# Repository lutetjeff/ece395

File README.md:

Repository for UIUC ECE395 project known as RHipoff. A mixture of the Rhythm Horizon and RE:Flex Dance platforms built from the ground up.
Current configuration is for four load cells only, but firmware supports up to 16 different panels with four load cells each.

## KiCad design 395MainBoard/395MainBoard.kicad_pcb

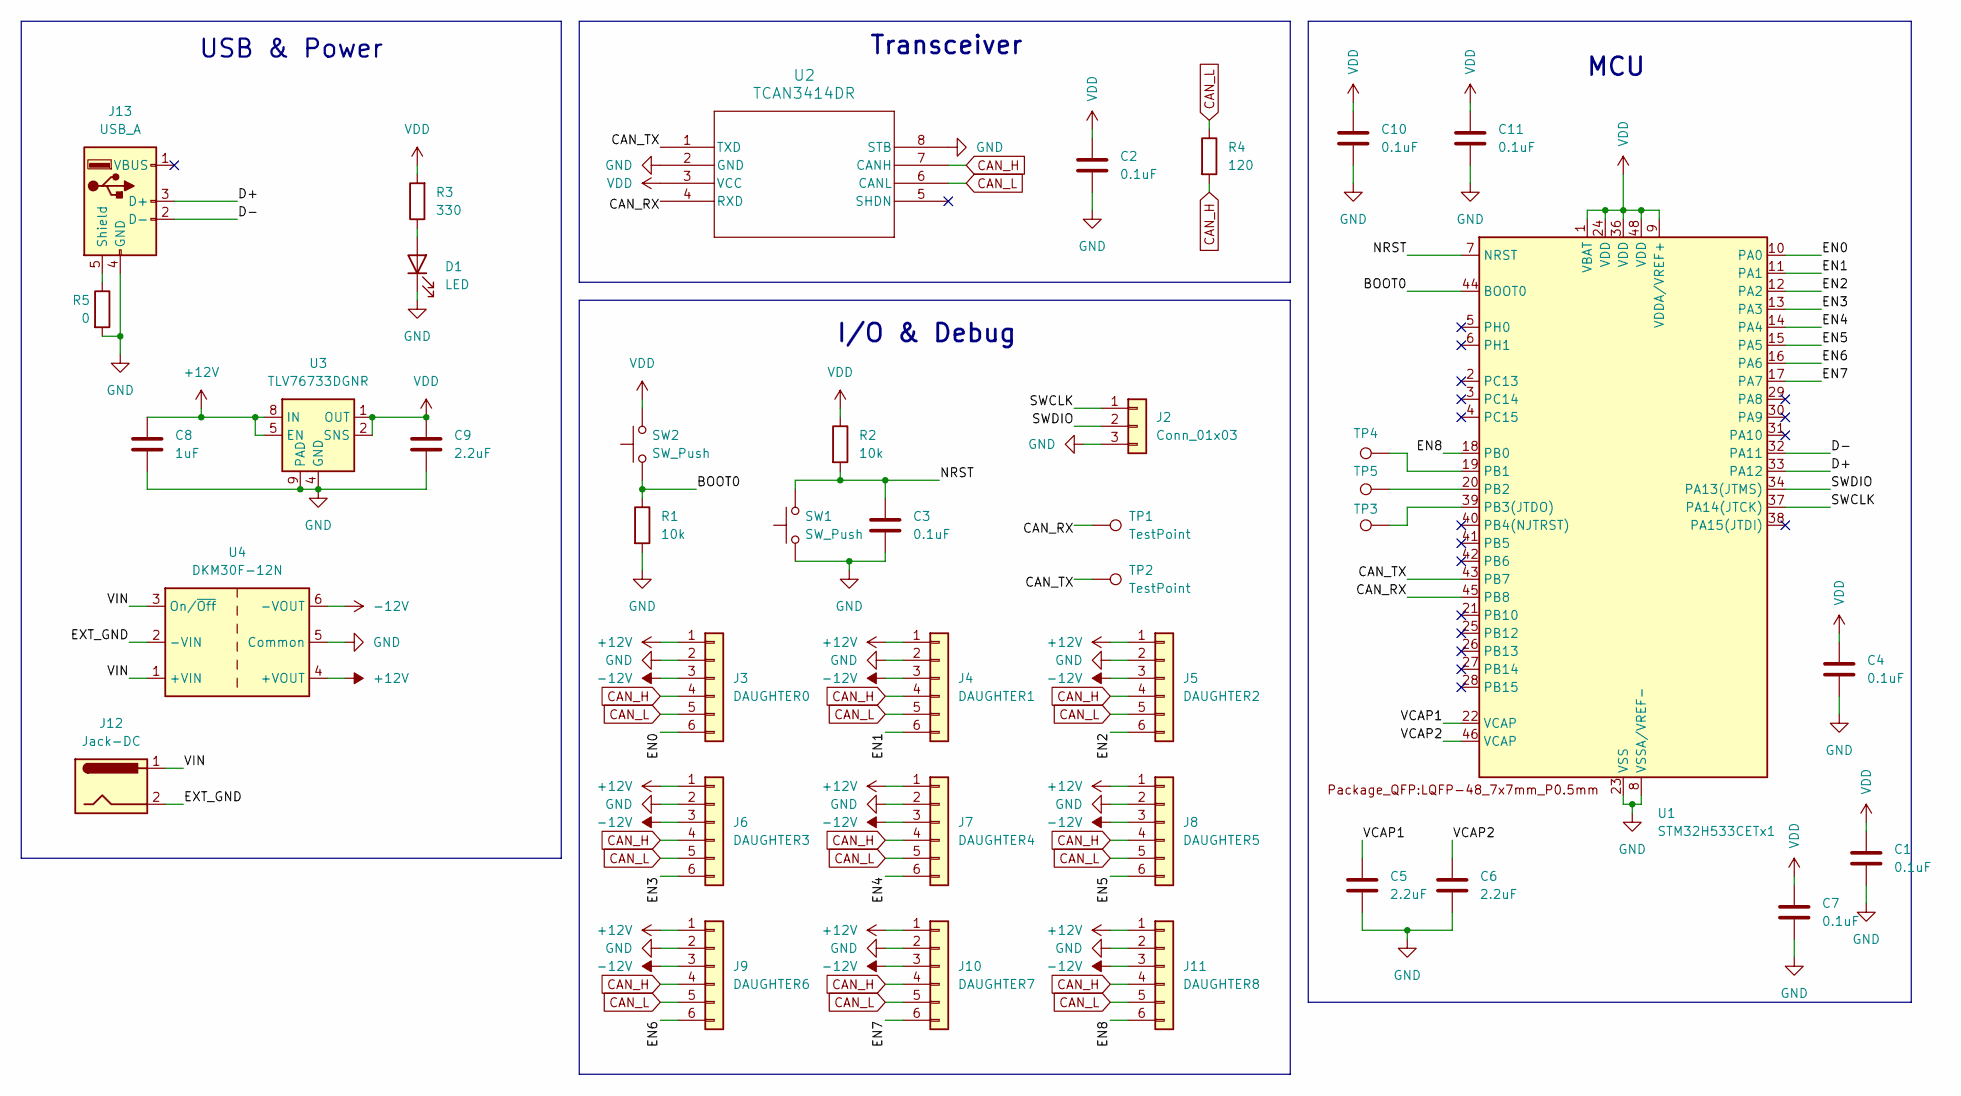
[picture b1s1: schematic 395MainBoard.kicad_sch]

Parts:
C1, C2, C3, C4, C7, C10, C11: 0.1uF; C_0805_2012Metric_Pad1.18x1.45mm_HandSolder
C5, C6, C9: 2.2uF; C_0805_2012Metric_Pad1.18x1.45mm_HandSolder
C8: 1uF; C_0805_2012Metric_Pad1.18x1.45mm_HandSolder
D1: LED; LED_0805_2012Metric_Pad1.15x1.40mm_HandSolder
J2: Conn_01x03; JST_XH_B3B-XH-A_1x03_P2.50mm_Vertical
J3: DAUGHTER0; JST_XH_B6B-XH-A_1x06_P2.50mm_Vertical
J4: DAUGHTER1; JST_XH_B6B-XH-A_1x06_P2.50mm_Vertical
J5: DAUGHTER2; JST_XH_B6B-XH-A_1x06_P2.50mm_Vertical
J6: DAUGHTER3; JST_XH_B6B-XH-A_1x06_P2.50mm_Vertical
J7: DAUGHTER4; JST_XH_B6B-XH-A_1x06_P2.50mm_Vertical
J8: DAUGHTER5; JST_XH_B6B-XH-A_1x06_P2.50mm_Vertical
J9: DAUGHTER6; JST_XH_B6B-XH-A_1x06_P2.50mm_Vertical
J10: DAUGHTER7; JST_XH_B6B-XH-A_1x06_P2.50mm_Vertical
J11: DAUGHTER8; JST_XH_B6B-XH-A_1x06_P2.50mm_Vertical
J12: Jack-DC; BarrelJack_Horizontal
J13: USB_A; USB_A_Molex_67643_Horizontal
R1, R2: 10k; R_0805_2012Metric_Pad1.20x1.40mm_HandSolder
R3: 330; R_0805_2012Metric_Pad1.20x1.40mm_HandSolder
R4: 120; R_0805_2012Metric_Pad1.20x1.40mm_HandSolder
R5: 0; R_0805_2012Metric_Pad1.20x1.40mm_HandSolder
SW1, SW2: SW_Push; SW_PUSH_6mm
TP1, TP2, TP3, TP4, TP5: TestPoint; TestPoint_Pad_D2.0mm
U1: STM32H533CETx1; LQFP-48_7x7mm_P0.5mm
U2: TCAN3414DR; SOIC-8_3.9x4.9mm_P1.27mm
U3: TLV76733DGNR; VSSOP-8_3x3mm_P0.65mm
U4: DKM30F-12N

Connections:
+12V: C8.1, J3.1, J4.1, J5.1, J6.1, J7.1, J8.1, J9.1, J10.1, J11.1, U3.5 (EN), U3.8 (IN), U4.4 (+VOUT)
-12V: J3.3, J4.3, J5.3, J6.3, J7.3, J8.3, J9.3, J10.3, J11.3, U4.6 (-VOUT)
/BOOT0: R1.1, SW2.1, U1.44 (BOOT0)
/CAN_RX: TP1.1, U1.45 (PB8), U2.4 (RXD)
/CAN_TX: TP2.1, U1.43 (PB7), U2.1 (TXD)
/D+: J13.3 (D+), U1.33 (PA12)
/D-: J13.2 (D-), U1.32 (PA11)
/EN0: J3.6, U1.10 (PA0)
/EN1: J4.6, U1.11 (PA1)
/EN2: J5.6, U1.12 (PA2)
/EN3: J6.6, U1.13 (PA3)
/EN4: J7.6, U1.14 (PA4)
/EN5: J8.6, U1.15 (PA5)
/EN6: J9.6, U1.16 (PA6)
/EN7: J10.6, U1.17 (PA7)
/EN8: J11.6, U1.18 (PB0)
/EXT_GND: J12.2, U4.2 (-VIN)
/NRST: C3.1, R2.2, SW1.2, U1.7 (NRST)
/SWCLK: J2.1, U1.37 (PA14(JTCK))
/SWDIO: J2.2, U1.34 (PA13(JTMS))
/VCAP1: C5.1, U1.22 (VCAP)
/VCAP2: C6.1, U1.46 (VCAP)
/VIN: J12.1, U4.1 (+VIN), U4.3 (On/~Off)
CAN_H: J3.4, J4.4, J5.4, J6.4, J7.4, J8.4, J9.4, J10.4, J11.4, R4.2, U2.7 (CANH)
CAN_L: J3.5, J4.5, J5.5, J6.5, J7.5, J8.5, J9.5, J10.5, J11.5, R4.1, U2.6 (CANL)
GND: C1.2, C2.2, C3.2, C4.2, C5.2, C6.2, C7.2, C8.2, C9.2, C10.2, C11.2, D1.1 (K), J2.3, J3.2, J4.2, J5.2, J6.2, J7.2, J8.2, J9.2, J10.2, J11.2, J13.4 (GND), R1.2, R5.2, SW1.1, U1.8 (VSSA/VREF-), U1.23 (VSS), U1.35 (VSS), U1.47 (VSS), U2.2 (GND), U2.8 (STB), U3.4 (GND), U3.6 (GND), U3.9 (PAD), U4.5 (Common)
unnamed: D1.2 (A), R3.1
unnamed: J13.5 (Shield), R5.1
unnamed: TP4.1, U1.19 (PB1)
unnamed: TP5.1, U1.20 (PB2)
unnamed: TP3.1, U1.39 (PB3(JTDO))
VDD: C1.1, C2.1, C4.1, C7.1, C9.1, C10.1, C11.1, R2.1, R3.2, SW2.2, U1.1 (VBAT), U1.9 (VDDA/VREF+), U1.24 (VDD), U1.36 (VDD), U1.48 (VDD), U2.3 (VCC), U3.1 (OUT), U3.2 (SNS)

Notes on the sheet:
I/O & Debug
USB & Power
Transceiver
MCU

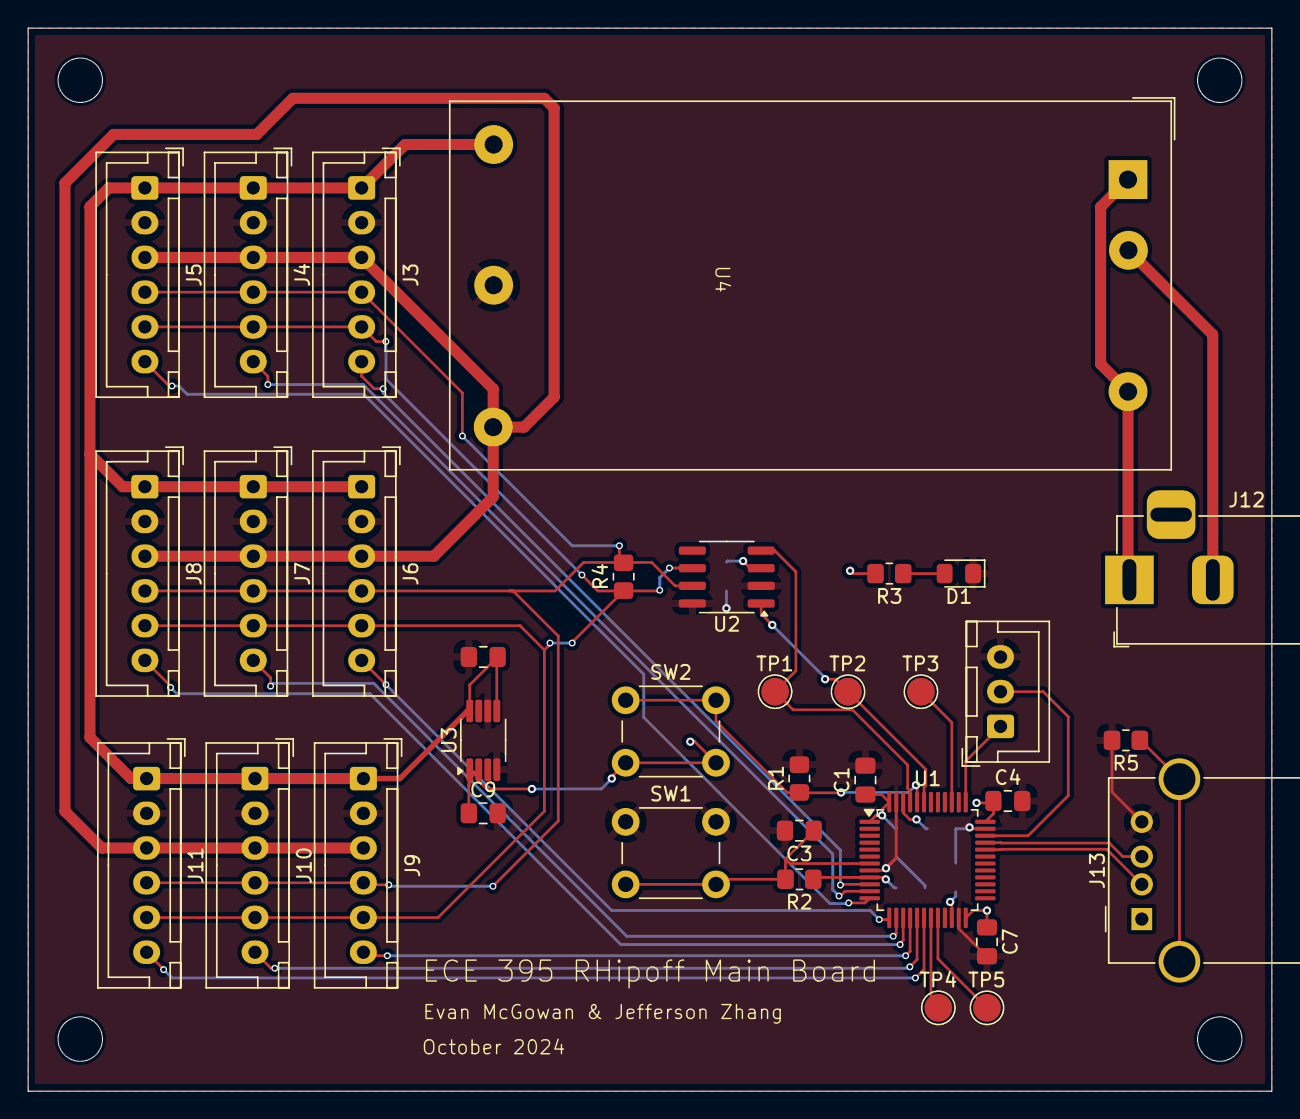
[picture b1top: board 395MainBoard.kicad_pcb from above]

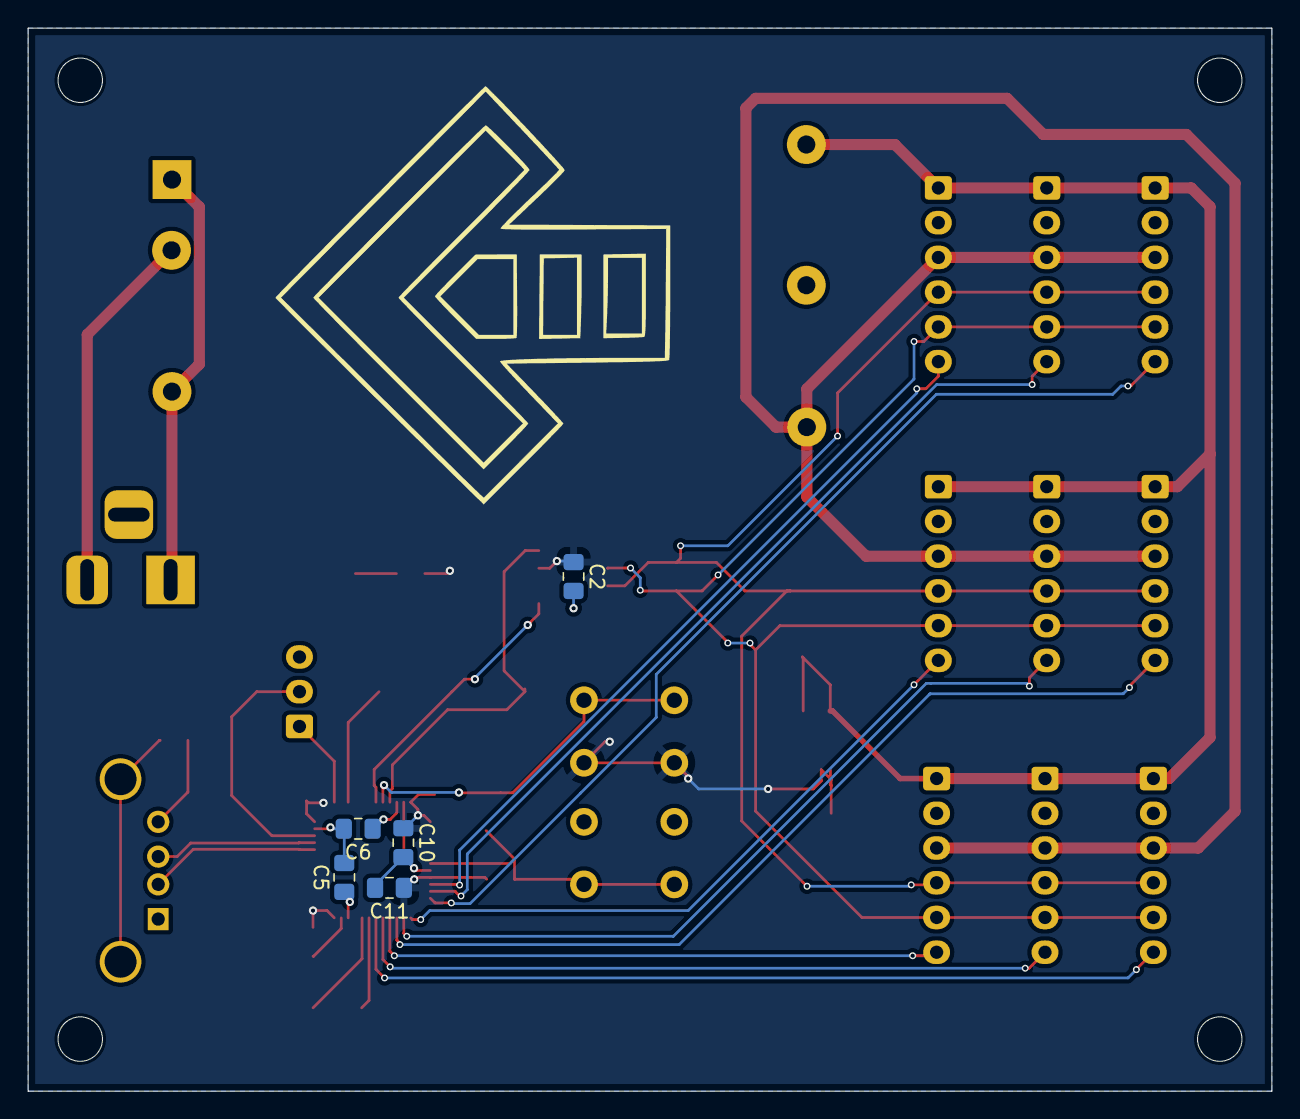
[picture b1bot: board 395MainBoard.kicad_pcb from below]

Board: 2 copper layers, 89.5 x 76.5 mm, 40 parts (5 on the bottom side), 32 nets.

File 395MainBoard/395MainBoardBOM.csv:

"Reference","Value","Datasheet","Footprint","Qty","DNP"
"C1,C2,C3,C4,C7,C10,C11","0.1uF","~","Capacitor_SMD:C_0805_2012Metric_Pad1.18x1.45mm_HandSolder","7",""
"C5,C6,C9","2.2uF","~","Capacitor_SMD:C_0805_2012Metric_Pad1.18x1.45mm_HandSolder","3",""
"C8","1uF","~","Capacitor_SMD:C_0805_2012Metric_Pad1.18x1.45mm_HandSolder","1",""
"D1","LED","~","LED_SMD:LED_0805_2012Metric_Pad1.15x1.40mm_HandSolder","1",""
"J2","Conn_01x03","~","Connector_JST:JST_XH_B3B-XH-A_1x03_P2.50mm_Vertical","1",""
"J3","DAUGHTER0","~","Connector_JST:JST_XH_B6B-XH-A_1x06_P2.50mm_Vertical","1",""
"J4","DAUGHTER1","~","Connector_JST:JST_XH_B6B-XH-A_1x06_P2.50mm_Vertical","1",""
"J5","DAUGHTER2","~","Connector_JST:JST_XH_B6B-XH-A_1x06_P2.50mm_Vertical","1",""
"J6","DAUGHTER3","~","Connector_JST:JST_XH_B6B-XH-A_1x06_P2.50mm_Vertical","1",""
"J7","DAUGHTER4","~","Connector_JST:JST_XH_B6B-XH-A_1x06_P2.50mm_Vertical","1",""
"J8","DAUGHTER5","~","Connector_JST:JST_XH_B6B-XH-A_1x06_P2.50mm_Vertical","1",""
"J9","DAUGHTER6","~","Connector_JST:JST_XH_B6B-XH-A_1x06_P2.50mm_Vertical","1",""
"J10","DAUGHTER7","~","Connector_JST:JST_XH_B6B-XH-A_1x06_P2.50mm_Vertical","1",""
"J11","DAUGHTER8","~","Connector_JST:JST_XH_B6B-XH-A_1x06_P2.50mm_Vertical","1",""
"J12","Jack-DC","~","Connector_BarrelJack:BarrelJack_Horizontal","1",""
"J13","USB_A","~","Connector_USB:USB_A_Molex_67643_Horizontal","1",""
"R1,R2","10k","~","Resistor_SMD:R_0805_2012Metric_Pad1.20x1.40mm_HandSolder","2",""
"R3","330","~","Resistor_SMD:R_0805_2012Metric_Pad1.20x1.40mm_HandSolder","1",""
"R4","120","~","Resistor_SMD:R_0805_2012Metric_Pad1.20x1.40mm_HandSolder","1",""
"R5","0","~","Resistor_SMD:R_0805_2012Metric_Pad1.20x1.40mm_HandSolder","1",""
"SW1,SW2","SW_Push","~","Button_Switch_THT:SW_PUSH_6mm","2",""
"TP1,TP2,TP3,TP4,TP5","TestPoint","~","TestPoint:TestPoint_Pad_D2.0mm","5",""
"U1","STM32H533CETx1","","Package_QFP:LQFP-48_7x7mm_P0.5mm","1",""
"U2","TCAN3414DR","PTCAN3414DR","Package_SO:SOIC-8_3.9x4.9mm_P1.27mm","1",""
"U3","TLV76733QWDRBxQ1","www.ti.com/lit/gpn/TLV767-q1","Package_SON:VSON-8-1EP_3x3mm_P0.65mm_EP1.65x2.4mm","1",""
"U4","DKM30F-12N","https://www.meanwell.com/webapp/product/search.aspx?prod=DKM30-N","Library:DKM30F-12N","1",""

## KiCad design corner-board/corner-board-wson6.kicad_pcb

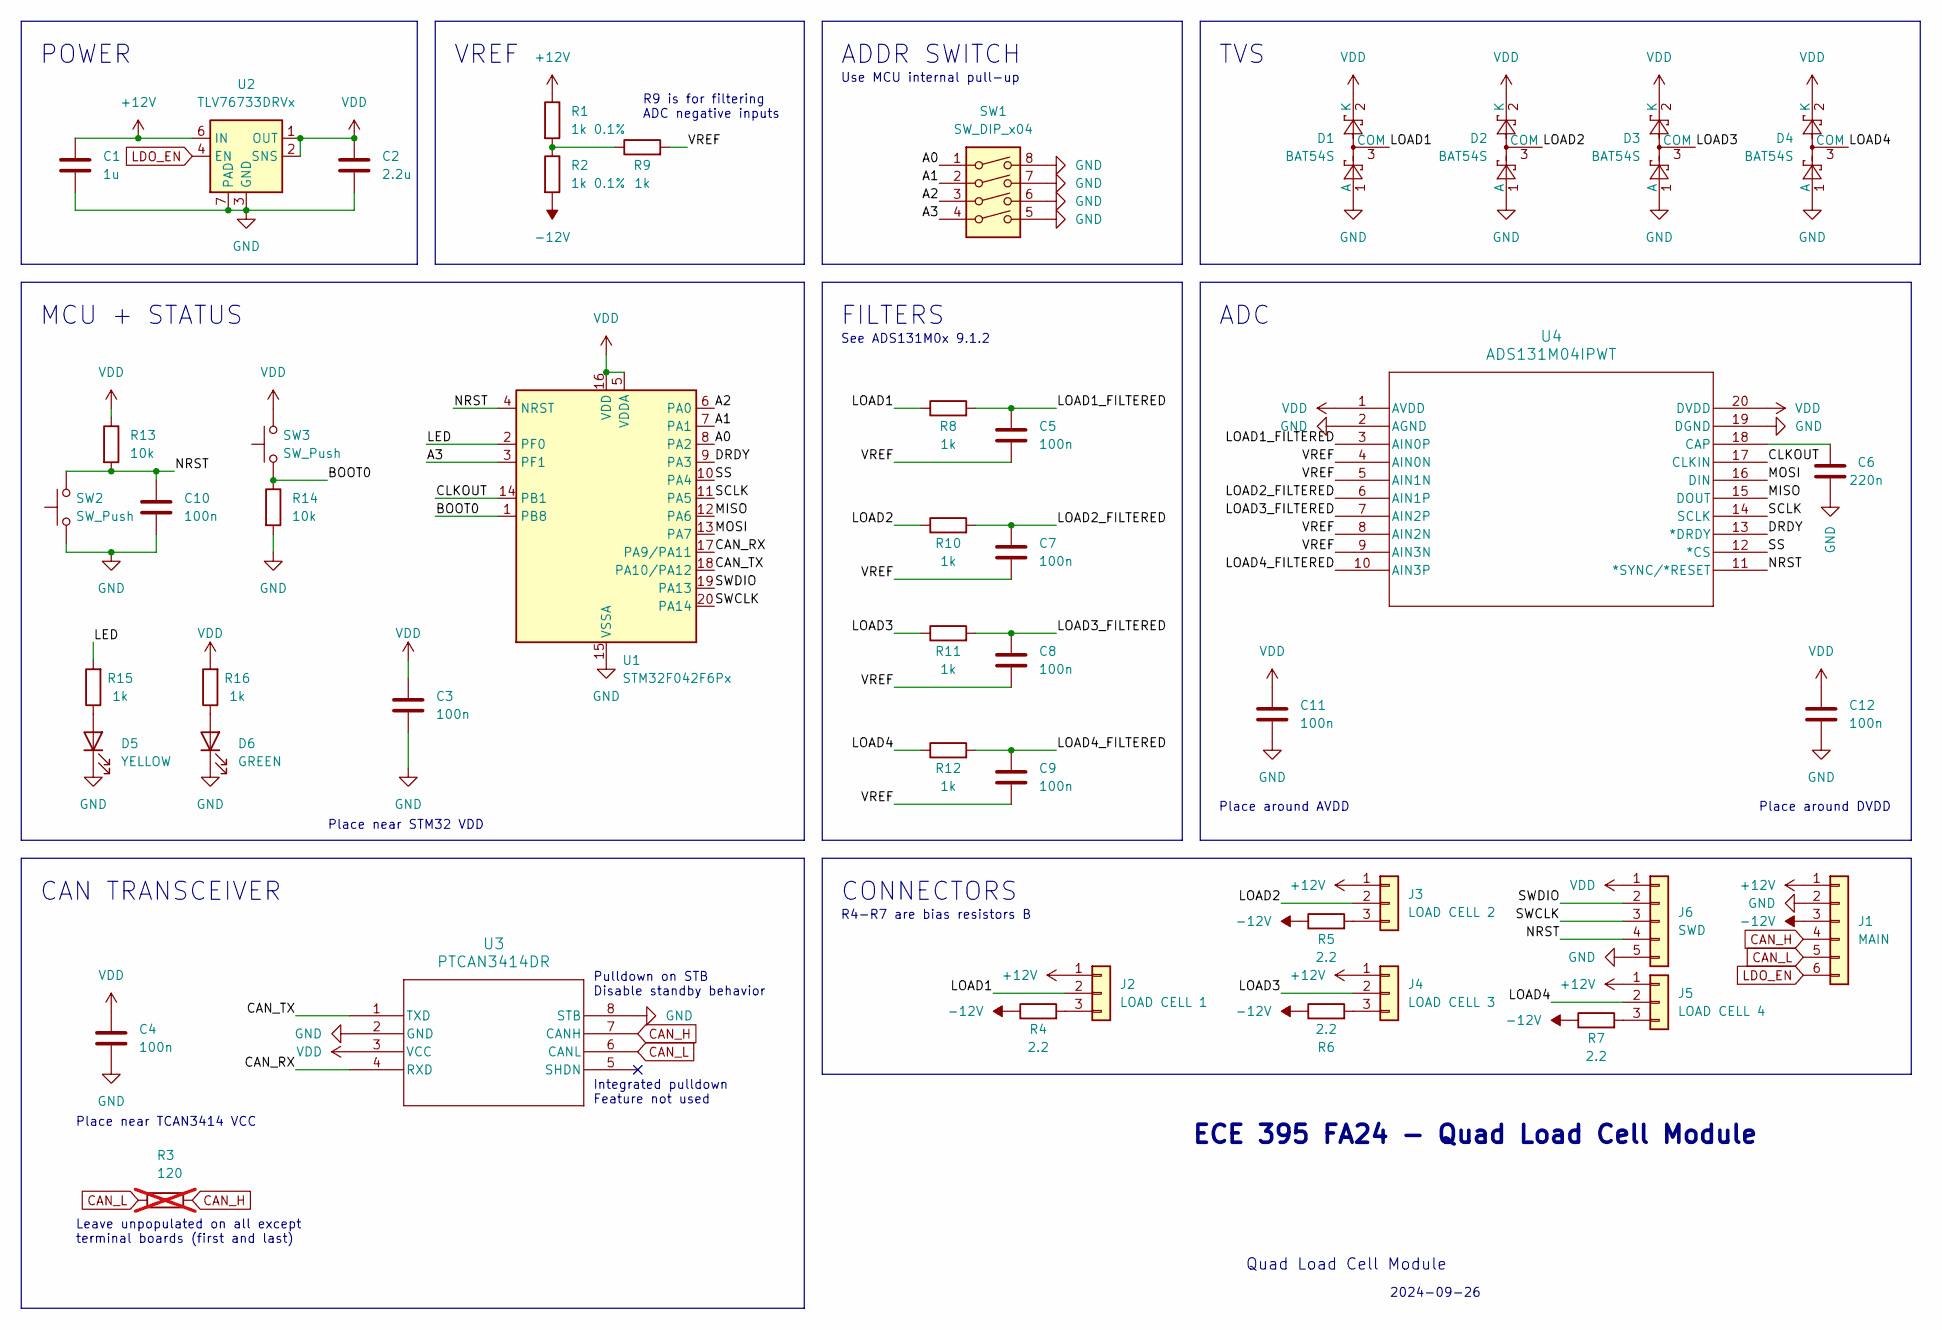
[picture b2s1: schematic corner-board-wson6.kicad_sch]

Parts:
C1: 1u; C_0805_2012Metric_Pad1.18x1.45mm_HandSolder; LCSC Part # C77386
C2: 2.2u; C_0805_2012Metric_Pad1.18x1.45mm_HandSolder; LCSC Part # C99227
C3, C4, C5, C7, C8, C9, C10, C11, C12: 100n; C_0603_1608Metric_Pad1.08x0.95mm_HandSolder; LCSC Part # C14663
C6: 220n; C_0805_2012Metric_Pad1.18x1.45mm_HandSolder; LCSC C77051
D1, D2, D3, D4: BAT54S; SOT-23; LCSC Part # C916425
D5: YELLOW; LED_0805_2012Metric_Pad1.15x1.40mm_HandSolder; LCSC Part # C2296
D6: GREEN; LED_0805_2012Metric_Pad1.15x1.40mm_HandSolder; LCSC Part # C2297
J1: MAIN; JST_XH_S6B-XH-A_1x06_P2.50mm_Horizontal
J2: LOAD CELL 1; JST_XH_S3B-XH-A_1x03_P2.50mm_Horizontal
J3: LOAD CELL 2; JST_XH_S3B-XH-A_1x03_P2.50mm_Horizontal
J4: LOAD CELL 3; JST_XH_S3B-XH-A_1x03_P2.50mm_Horizontal
J5: LOAD CELL 4; JST_XH_S3B-XH-A_1x03_P2.50mm_Horizontal
J6: SWD; PinHeader_1x05_P2.54mm_Vertical
R1, R2: 1k 0.1%; R_0603_1608Metric_Pad0.98x0.95mm_HandSolder; LCSC Part # C110776
R3: 120; R_0603_1608Metric_Pad0.98x0.95mm_HandSolder; not fitted
R4, R5, R6, R7: 2.2; R_0603_1608Metric_Pad0.98x0.95mm_HandSolder; LCSC Part # C25226
R8, R9, R10, R11, R12, R15, R16: 1k; R_0603_1608Metric_Pad0.98x0.95mm_HandSolder; LCSC Part # C21190
R13, R14: 10k; R_0603_1608Metric_Pad0.98x0.95mm_HandSolder; LCSC Part # C25804
SW1: SW_DIP_x04; SW_DIP_SPSTx04_Slide_6.7x11.72mm_W7.62mm_P2.54mm_LowProfile
SW2, SW3: SW_Push; SW_PUSH_6mm
U1: STM32F042F6Px; TSSOP-20_4.4x6.5mm_P0.65mm; LCSC Part # C81000
U2: TLV76733DRVx; WSON-6-1EP_2x2mm_P0.65mm_EP1x1.6mm_ThermalVias; LCSC Part # C2848334
U3: PTCAN3414DR; SOIC8_D_TEX; LCSC Part # C189939
U4: ADS131M04IPWT; PW20_TEX; LCSC Part # C2862562

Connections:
+12V: C1.1, J1.1, J2.1, J3.1, J4.1, J5.1, R1.1, U2.6 (IN)
-12V: J1.3, R2.2, R4.1, R5.1, R6.1, R7.1
/A0: SW1.1, U1.8 (PA2)
/A1: SW1.2, U1.7 (PA1)
/A2: SW1.3, U1.6 (PA0)
/A3: SW1.4, U1.3 (PF1)
/BOOT0: R14.1, SW3.1, U1.1 (PB8)
/CAN_RX: U1.17 (PA9/PA11), U3.4 (RXD)
/CAN_TX: U1.18 (PA10/PA12), U3.1 (TXD)
/CLKOUT: U1.14 (PB1), U4.17 (CLKIN)
/DRDY: U1.9 (PA3), U4.13 (*DRDY)
/LED: R15.2, U1.2 (PF0)
/LOAD1: D1.3 (COM), J2.2, R8.1
/LOAD1_FILTERED: C5.1, R8.2, U4.3 (AIN0P)
/LOAD2: D2.3 (COM), J3.2, R10.1
/LOAD2_FILTERED: C7.1, R10.2, U4.6 (AIN1P)
/LOAD3: D3.3 (COM), J4.2, R11.1
/LOAD3_FILTERED: C8.1, R11.2, U4.7 (AIN2P)
/LOAD4: D4.3 (COM), J5.2, R12.1
/LOAD4_FILTERED: C9.1, R12.2, U4.10 (AIN3P)
/MISO: U1.12 (PA6), U4.15 (DOUT)
/MOSI: U1.13 (PA7), U4.16 (DIN)
/NRST: C10.1, J6.4, R13.2, SW2.2, U1.4 (NRST), U4.11 (*SYNC/*RESET)
/SCLK: U1.11 (PA5), U4.14 (SCLK)
/SS: U1.10 (PA4), U4.12 (*CS)
/SWCLK: J6.3, U1.20 (PA14)
/SWDIO: J6.2, U1.19 (PA13)
/VREF: C5.2, C7.2, C8.2, C9.2, R9.2, U4.4 (AIN0N), U4.5 (AIN1N), U4.8 (AIN2N), U4.9 (AIN3N)
CAN_H: J1.4, R3.1, U3.7 (CANH)
CAN_L: J1.5, R3.2, U3.6 (CANL)
GND: C1.2, C2.2, C3.2, C4.2, C6.2, C10.2, C11.2, C12.2, D1.1 (A), D2.1 (A), D3.1 (A), D4.1 (A), D5.1 (K), D6.1 (K), J1.2, J6.5, R14.2, SW1.5, SW1.6, SW1.7, SW1.8, SW2.1, U1.15 (VSSA), U2.3 (GND), U2.5 (GND), U2.7 (PAD), U3.2 (GND), U3.8 (STB), U4.2 (AGND), U4.19 (DGND)
LDO_EN: J1.6, U2.4 (EN)
unnamed: D5.2 (A), R15.1
unnamed: D6.2 (A), R16.1
unnamed: J2.3, R4.2
unnamed: J3.3, R5.2
unnamed: J4.3, R6.2
unnamed: J5.3, R7.2
unnamed: R1.2, R2.1, R9.1
unnamed: C6.1, U4.18 (CAP)
VDD: C2.1, C3.1, C4.1, C11.1, C12.1, D1.2 (K), D2.2 (K), D3.2 (K), D4.2 (K), J6.1, R13.1, R16.2, SW3.2, U1.5 (VDDA), U1.16 (VDD), U2.1 (OUT), U2.2 (SNS), U3.3 (VCC), U4.1 (AVDD), U4.20 (DVDD)

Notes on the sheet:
CONNECTORS
MCU + STATUS
VREF
Use MCU internal pull-up
Place near STM32 VDD
Leave unpopulated on all except terminal boards (first and last)
ECE 395 FA24 - Quad Load Cell Module
POWER
FILTERS
Place around AVDD
See ADS131M0x 9.1.2
Pulldown on STB Disable standby behavior
ADDR SWITCH
CAN TRANSCEIVER
Quad Load Cell Module
2024-09-26
Place near TCAN3414 VCC
Place around DVDD
R9 is for filtering ADC negative inputs
ADC
R4-R7 are bias resistors B
TVS
Integrated pulldown Feature not used

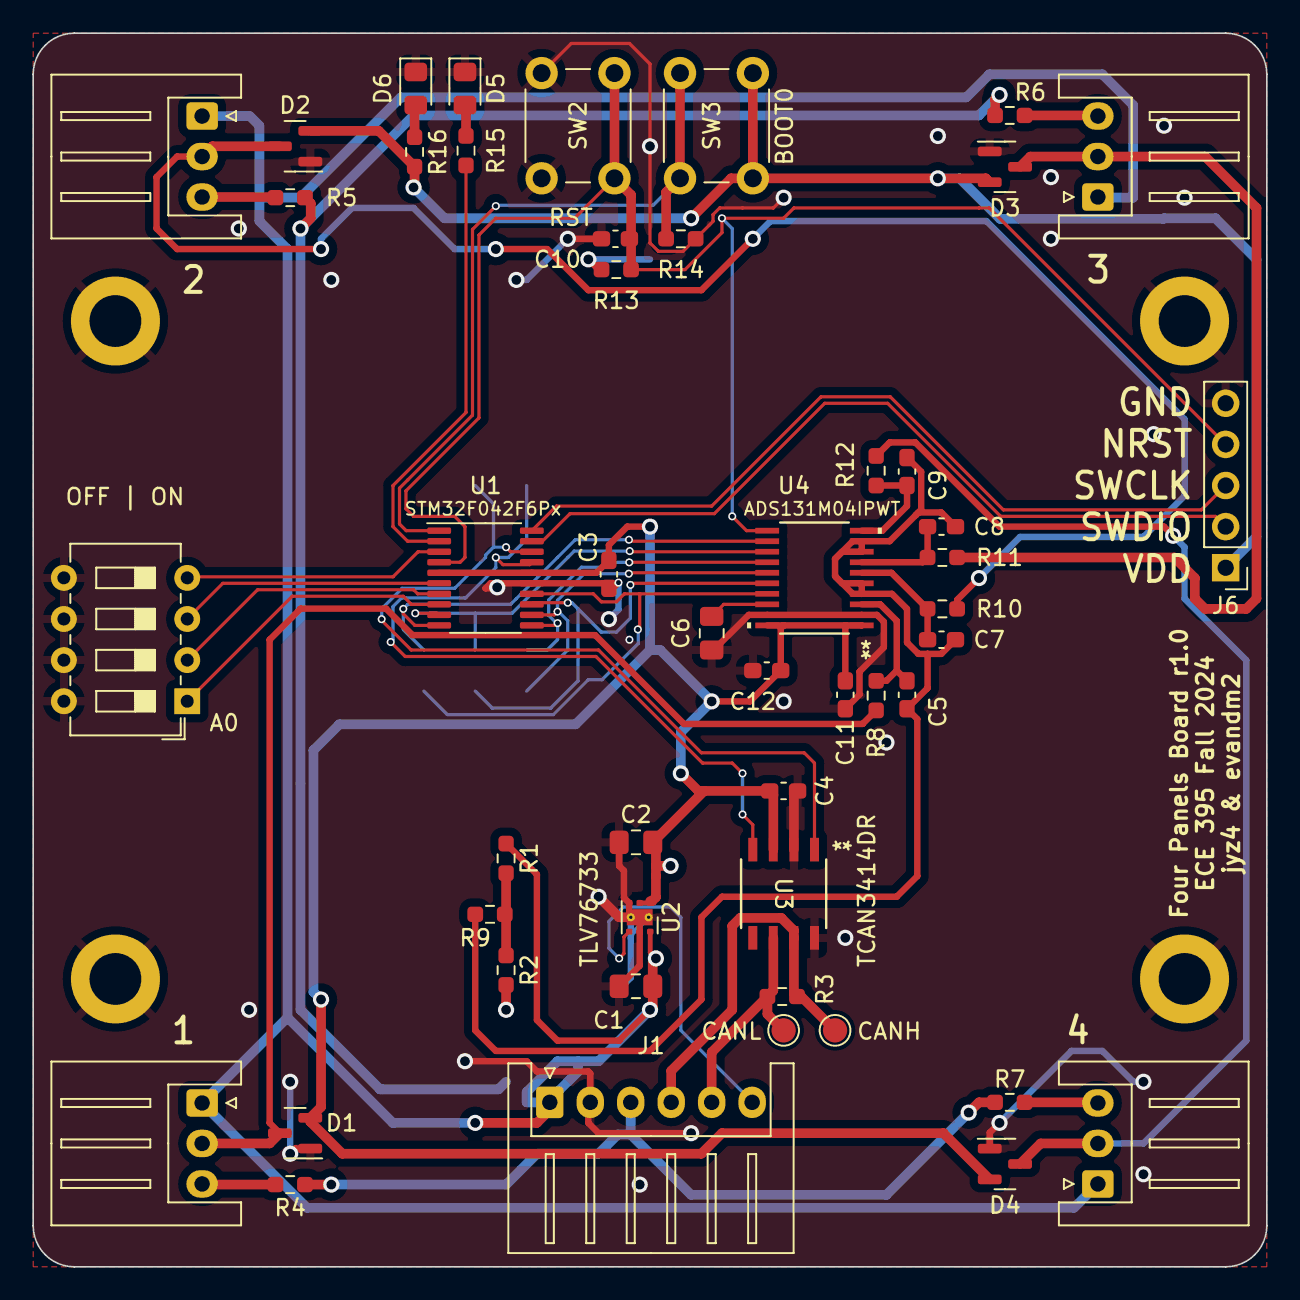
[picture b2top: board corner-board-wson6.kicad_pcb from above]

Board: 2 copper layers, 76.2 x 76.2 mm, 47 parts (0 on the bottom side), 41 nets.

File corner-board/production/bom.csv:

Designator,Footprint,Quantity,Value,LCSC Part #
C1,805,1,1u,C77386
"C10, C11, C12, C3, C4, C5, C7, C8, C9",603,9,100n,C14663
C2,805,1,2.2u,C99227
C6,805,1,220n,C77051
"D1, D2, D3, D4",SOT-23,4,BAT54S,C916425
D5,805,1,YELLOW,C2296
D6,805,1,GREEN,C2297
"R1, R2",603,2,1k 0.1%,C110776
"R10, R11, R12, R15, R16, R8, R9",603,7,1k,C21190
"R13, R14",603,2,10k,C25804
"R4, R5, R6, R7",603,4,2.2,C25226
U1,TSSOP-20_4.4x6.5mm_P0.65mm,1,STM32F042F6Px,C81000
U2,WSON-6-1EP_2x2mm_P0.65mm_EP1x1.6mm_ThermalVias,1,TLV76733DRVx,C2848334
U3,SOIC8_D_TEX,1,PTCAN3414DR,C189939
U4,PW20_TEX,1,ADS131M04IPWT,C2862562
,,,,
,,,,

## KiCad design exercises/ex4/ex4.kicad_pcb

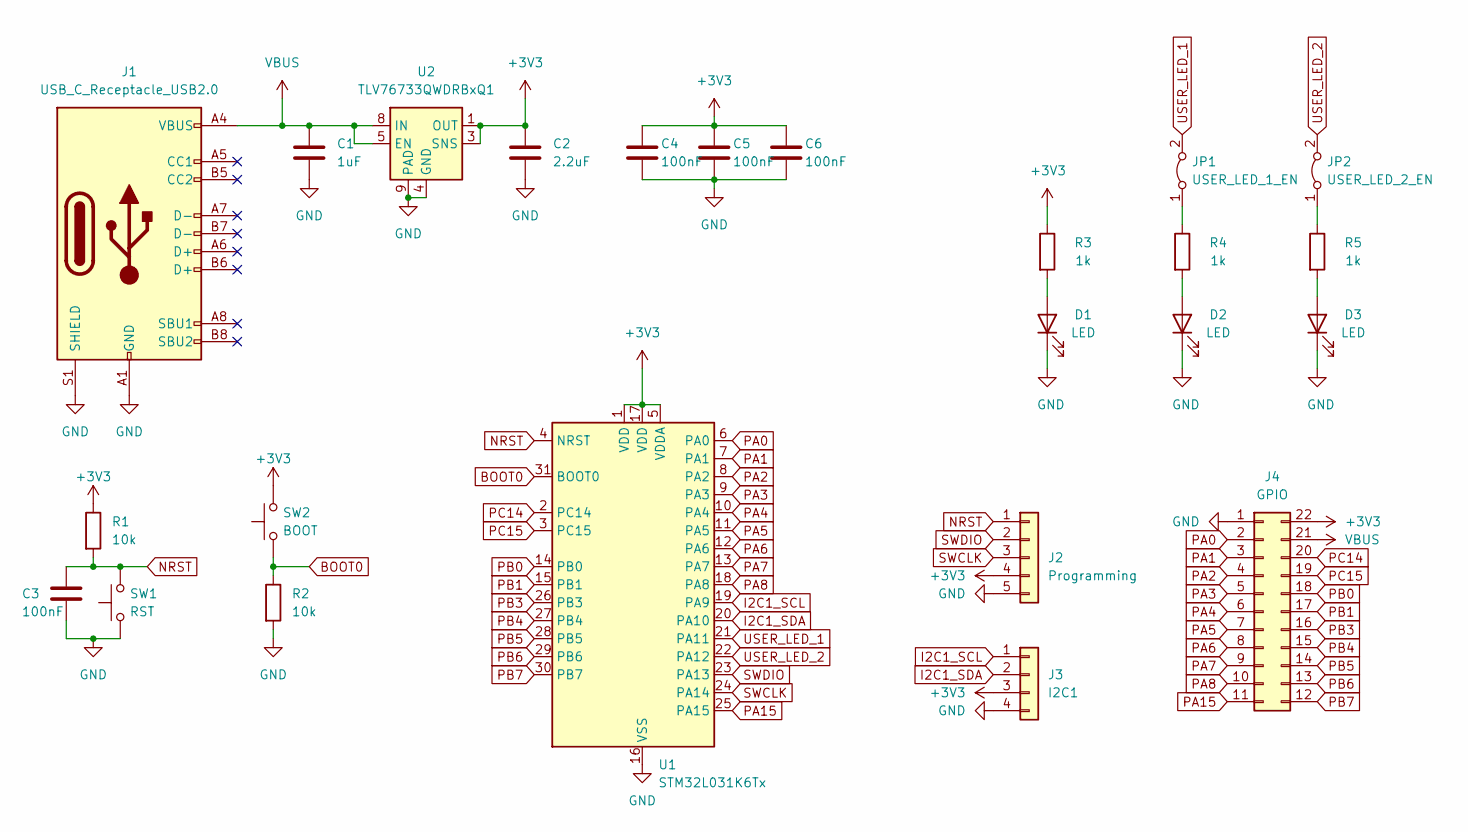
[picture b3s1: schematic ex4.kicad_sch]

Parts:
C1: 1uF; C_0805_2012Metric_Pad1.18x1.45mm_HandSolder
C2: 2.2uF; C_0805_2012Metric_Pad1.18x1.45mm_HandSolder
C3, C4, C5, C6: 100nF; C_0805_2012Metric_Pad1.18x1.45mm_HandSolder
D1, D2, D3: LED; LED_0805_2012Metric_Pad1.15x1.40mm_HandSolder
J1: USB_C_Receptacle_USB2.0; USB_C_Receptacle_GCT_USB4085
J2: Programming; PinHeader_1x05_P2.54mm_Vertical
J3: I2C1; PinHeader_1x04_P2.54mm_Vertical
J4: GPIO; PinHeader_2x11_P2.54mm_Vertical
JP1: USER_LED_1_EN; SolderJumper-2_P1.3mm_Bridged2Bar_RoundedPad1.0x1.5mm
JP2: USER_LED_2_EN; SolderJumper-2_P1.3mm_Bridged2Bar_RoundedPad1.0x1.5mm
R1, R2: 10k; R_0805_2012Metric_Pad1.20x1.40mm_HandSolder
R3, R4, R5: 1k; R_0805_2012Metric_Pad1.20x1.40mm_HandSolder
SW1: RST; SW_SPST_PTS810
SW2: BOOT; SW_SPST_PTS810
U1: STM32L031K6Tx; LQFP-32_7x7mm_P0.8mm
U2: TLV76733QWDRBxQ1; VSON-8-1EP_3x3mm_P0.65mm_EP1.65x2.4mm

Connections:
+3V3: C2.1, C4.1, C5.1, C6.1, J2.4, J3.3, J4.22, R1.1, R3.1, SW2.2, U1.1 (VDD), U1.5 (VDDA), U1.17 (VDD), U2.1 (OUT), U2.3 (SNS)
BOOT0: R2.1, SW2.1, U1.31 (BOOT0)
GND: C1.2, C2.2, C3.2, C4.2, C5.2, C6.2, D1.1 (K), D2.1 (K), D3.1 (K), J1.A1 (GND), J1.A12 (GND), J1.B1 (GND), J1.B12 (GND), J1.S1 (SHIELD), J2.5, J3.4, J4.1, R2.2, SW1.1, U1.16 (VSS), U1.32 (VSS), U2.4 (GND), U2.6 (GND), U2.9 (PAD)
I2C1_SCL: J3.1, U1.19 (PA9)
I2C1_SDA: J3.2, U1.20 (PA10)
NRST: C3.1, J2.1, R1.2, SW1.2, U1.4 (NRST)
unnamed: D1.2 (A), R3.2
unnamed: D2.2 (A), R4.2
unnamed: D3.2 (A), R5.2
unnamed: JP1.1 (A), R4.1
unnamed: JP2.1 (A), R5.1
PA0: J4.2, U1.6 (PA0)
PA1: J4.3, U1.7 (PA1)
PA2: J4.4, U1.8 (PA2)
PA3: J4.5, U1.9 (PA3)
PA4: J4.6, U1.10 (PA4)
PA5: J4.7, U1.11 (PA5)
PA6: J4.8, U1.12 (PA6)
PA7: J4.9, U1.13 (PA7)
PA8: J4.10, U1.18 (PA8)
PA15: J4.11, U1.25 (PA15)
PB0: J4.18, U1.14 (PB0)
PB1: J4.17, U1.15 (PB1)
PB3: J4.16, U1.26 (PB3)
PB4: J4.15, U1.27 (PB4)
PB5: J4.14, U1.28 (PB5)
PB6: J4.13, U1.29 (PB6)
PB7: J4.12, U1.30 (PB7)
PC14: J4.20, U1.2 (PC14)
PC15: J4.19, U1.3 (PC15)
SWCLK: J2.3, U1.24 (PA14)
SWDIO: J2.2, U1.23 (PA13)
USER_LED_1: JP1.2 (B), U1.21 (PA11)
USER_LED_2: JP2.2 (B), U1.22 (PA12)
VBUS: C1.1, J1.A4 (VBUS), J1.A9 (VBUS), J1.B4 (VBUS), J1.B9 (VBUS), J4.21, U2.5 (EN), U2.8 (IN)

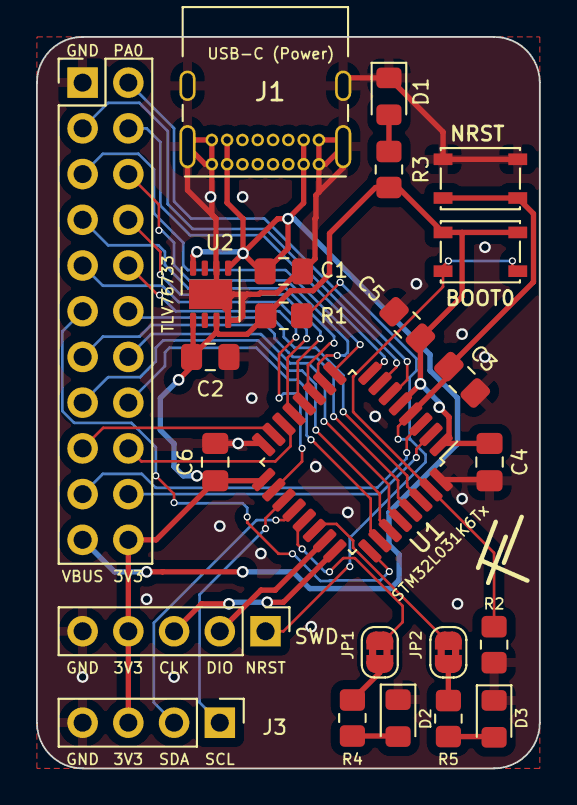
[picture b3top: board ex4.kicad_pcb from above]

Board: 2 copper layers, 27.9 x 40.6 mm, 24 parts (0 on the bottom side), 35 nets.

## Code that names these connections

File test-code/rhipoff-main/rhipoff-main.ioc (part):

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Mcu.Name=STM32H533CETx
Mcu.Package=LQFP48
Mcu.UserName=STM32H533CETx
PA0.Signal=GPIO_Output
PA1.Signal=GPIO_Output
PA11.Mode=Device
PA11.Signal=USB_DM
PA12.Mode=Device
PA12.Signal=USB_DP
PA13(JTMS/SWDIO).Signal=DEBUG_JTMS-SWDIO
PA14(JTCK/SWCLK).Signal=DEBUG_JTCK-SWCLK
PA2.Signal=GPIO_Output
PA3.Signal=GPIO_Output
PA4.Signal=GPIO_Output
PA5.Signal=GPIO_Output
PA6.Signal=GPIO_Output
PA7.Signal=GPIO_Output
PB0.Signal=GPIO_Output
PB1.Signal=GPIO_Output
PB2.Signal=GPIO_Output
PB3(JTDO/TRACESWO).Signal=GPIO_Output
PB7.Mode=FDCAN_Activate
PB7.Signal=FDCAN1_TX
PB8.Mode=FDCAN_Activate
PB8.Signal=FDCAN1_RX
RCC.HSE_VALUE=25000000
RCC.SYSCLKFreq_VALUE=250000000
RCC.SYSCLKSource=RCC_SYSCLKSOURCE_PLLCLK
board=custom

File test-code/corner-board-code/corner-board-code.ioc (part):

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Mcu.Name=STM32F042F6Px
Mcu.Package=TSSOP20
Mcu.UserName=STM32F042F6Px
PA0.GPIOParameters=GPIO_PuPd,GPIO_Label
PA0.GPIO_Label=A2
PA0.GPIO_PuPd=GPIO_PULLUP
PA0.Signal=GPIO_Input
PA1.GPIOParameters=GPIO_PuPd,GPIO_Label
PA1.GPIO_Label=A1
PA1.GPIO_PuPd=GPIO_PULLUP
PA1.Signal=GPIO_Input
PA11.Mode=CAN_Activate
PA11.Signal=CAN_RX
PA12.Mode=CAN_Activate
PA12.Signal=CAN_TX
PA2.GPIOParameters=GPIO_PuPd,GPIO_Label
PA2.GPIO_Label=A0
PA2.GPIO_PuPd=GPIO_PULLUP
PA2.Signal=GPIO_Input
PA3.GPIOParameters=GPIO_Label,GPIO_ModeDefaultEXTI
PA3.GPIO_Label=DRDY
PA3.GPIO_ModeDefaultEXTI=GPIO_MODE_IT_FALLING
PA3.Signal=GPXTI3
PA4.GPIOParameters=GPIO_Label
PA4.GPIO_Label=CS
PA4.Signal=GPIO_Output
PA5.Mode=Full_Duplex_Master
PA5.Signal=SPI1_SCK
PA6.Mode=Full_Duplex_Master
PA6.Signal=SPI1_MISO
PA7.Mode=Full_Duplex_Master
PA7.Signal=SPI1_MOSI
PB1.GPIOParameters=GPIO_Label
PB1.GPIO_Label=CLKOUT
PB1.Signal=S_TIM3_CH4
PF0-OSC_IN.GPIOParameters=GPIO_Label
PF0-OSC_IN.GPIO_Label=LED
PF0-OSC_IN.Signal=GPIO_Output
PF1-OSC_OUT.GPIOParameters=GPIO_PuPd,GPIO_Label
PF1-OSC_OUT.GPIO_Label=A3
PF1-OSC_OUT.GPIO_PuPd=GPIO_PULLUP
PF1-OSC_OUT.Signal=GPIO_Input
RCC.SYSCLKFreq_VALUE=48000000
RCC.SYSCLKSource=RCC_SYSCLKSOURCE_PLLCLK
board=custom

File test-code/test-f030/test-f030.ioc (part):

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Mcu.Name=STM32F030R8Tx
Mcu.Package=LQFP64
Mcu.UserName=STM32F030R8Tx
PA0.Mode=IN0
PA0.Signal=ADC_IN0
PA1.Mode=IN1
PA1.Signal=ADC_IN1
PA13.GPIOParameters=GPIO_Label
PA13.GPIO_Label=TMS
PA13.Mode=Serial_Wire
PA13.Signal=SYS_SWDIO
PA14.GPIOParameters=GPIO_Label
PA14.GPIO_Label=TCK
PA14.Mode=Serial_Wire
PA14.Signal=SYS_SWCLK
PA2.GPIOParameters=GPIO_Speed,GPIO_PuPd,GPIO_Label,GPIO_Mode
PA2.GPIO_Label=USART_TX
PA2.GPIO_Mode=GPIO_MODE_AF_PP
PA2.GPIO_PuPd=GPIO_NOPULL
PA2.GPIO_Speed=GPIO_SPEED_FREQ_LOW
PA2.Mode=Asynchronous
PA2.Signal=USART2_TX
PA3.GPIOParameters=GPIO_Speed,GPIO_PuPd,GPIO_Label,GPIO_Mode
PA3.GPIO_Label=USART_RX
PA3.GPIO_Mode=GPIO_MODE_AF_PP
PA3.GPIO_PuPd=GPIO_NOPULL
PA3.GPIO_Speed=GPIO_SPEED_FREQ_LOW
PA3.Mode=Asynchronous
PA3.Signal=USART2_RX
PA4.Mode=IN4
PA4.Signal=ADC_IN4
PA5.GPIOParameters=GPIO_Speed,GPIO_PuPd,GPIO_Label,GPIO_Mode
PA5.GPIO_Label=LD2 [Green Led]
PA5.GPIO_Mode=GPIO_MODE_OUTPUT_PP
PA5.GPIO_PuPd=GPIO_NOPULL
PA5.GPIO_Speed=GPIO_SPEED_FREQ_LOW
PA5.Signal=GPIO_Output
PB0.Mode=IN8
PB0.Signal=ADC_IN8
PC13.GPIOParameters=GPIO_Label,GPIO_ModeDefaultEXTI
PC13.GPIO_Label=B1 [Blue PushButton]
PC13.GPIO_ModeDefaultEXTI=GPIO_MODE_IT_FALLING
PC13.Signal=GPXTI13
PC14-OSC32_IN.Mode=LSE-External-Oscillator
PC14-OSC32_IN.Signal=RCC_OSC32_IN
PC15-OSC32_OUT.Mode=LSE-External-Oscillator
PC15-OSC32_OUT.Signal=RCC_OSC32_OUT
PF0-OSC_IN.Mode=HSE-External-Clock-Source
PF0-OSC_IN.Signal=RCC_OSC_IN
PF1-OSC_OUT.Signal=RCC_OSC_OUT
RCC.SYSCLKFreq_VALUE=48000000
RCC.SYSCLKSource=RCC_SYSCLKSOURCE_PLLCLK
board=NUCLEO-F030R8
boardIOC=true

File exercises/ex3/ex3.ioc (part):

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Mcu.Name=STM32L031K(4-6)Tx
Mcu.Package=LQFP32
Mcu.UserName=STM32L031K6Tx
PA10.Mode=I2C
PA10.Signal=I2C1_SDA
PA2.Mode=Asynchronous
PA2.Signal=LPUART1_TX
PA3.Mode=Asynchronous
PA3.Signal=LPUART1_RX
PA9.Mode=I2C
PA9.Signal=I2C1_SCL
PB0.GPIOParameters=GPIO_Label
PB0.GPIO_Label=LED
PB0.Signal=GPIO_Output
RCC.HSE_VALUE=8000000
RCC.SYSCLKFreq_VALUE=2097000
board=custom

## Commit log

2024-10-28 10-28
2024-10-30 working api
2024-10-30 add drdy interrupt
2024-11-05 can working but not fast enough
2024-11-10 Boilerplate code for USB finished
2024-11-11 can fix, 38.8% bus load lolw
2024-11-14 USB boilerplate ACTUALLY done
    took the L and did the code in CubeIDE but it works
2024-11-19 CAN it? It CAN!
    Began work on the CAN protocol for main board and getting data out to USB CDC
2024-11-19 reduced to standard CAN, bus load at 8%
2024-11-19 freq back up to 1khz
2024-12-03 Reading from CAN!
2024-12-04 12/03
2024-12-06 Attempting to implement CustomHID class
    Got most of the way there (I think) and did a bilinear interpolation exercise that didn't prove helpful...we have four data points after all. Different method should likely be used if any
2024-12-09 HID kind of functional
    Gamepad works, but I can't get HID & CDC to cooperate together...yet. Something about the composite building is causing problems.
2024-12-10 IT IS DONE!
    Project is finished. CustomHID & CDC are functional together. Sensitivity offsets are good for stepping
2024-12-14 Likely final commit
    Added main board KiCad files to repo and reorganized a bit
2024-12-14 Added CAD files
    Prototype CAD files & drawings now included in repository for reproduction.
